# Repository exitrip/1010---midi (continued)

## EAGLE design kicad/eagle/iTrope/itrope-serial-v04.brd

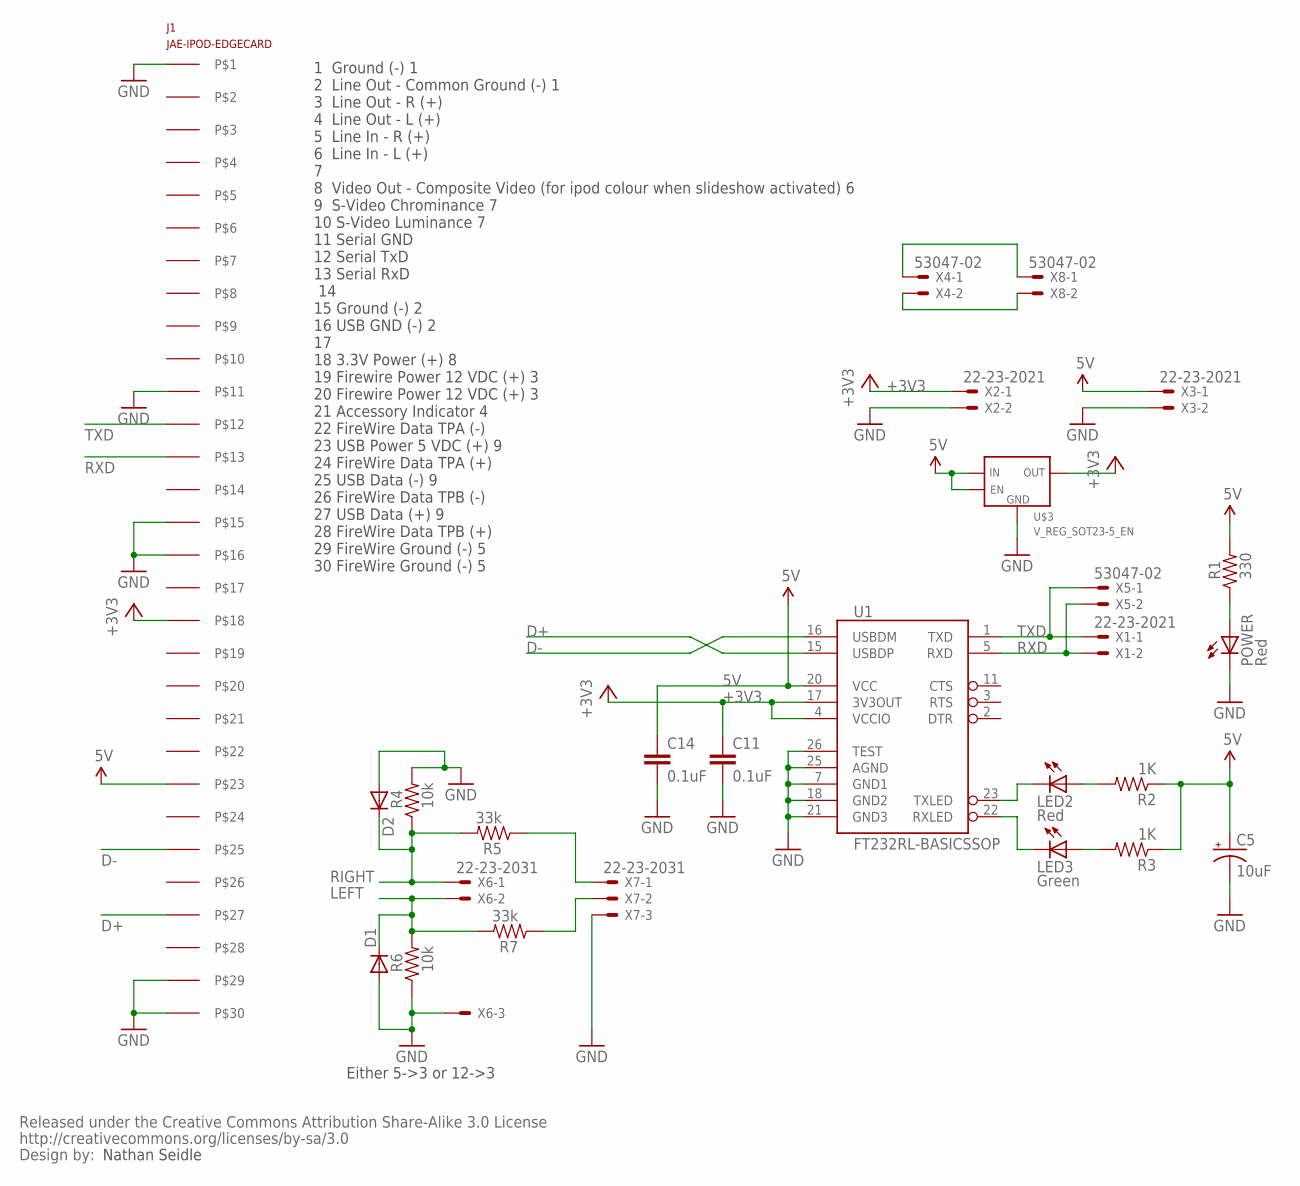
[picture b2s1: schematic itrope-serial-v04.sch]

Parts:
C5: 10uF; EIA3216
C11, C14: 0.1uF; C0402
D1, D2: DIODESOD; SOD-323
J1: JAE-IPOD-EDGECARD; 30PINEDGE
LED2: Red; LED-0603
LED3: Green; LED-0603
POWER: Red; LED-0603
R1: 330; C0402
R2, R3: 1K; C0402
R4, R6: 10k; C0402
R5, R7: 33k; C0402
U1: FT232RL-BASICSSOP; SSOP28DB
U$3: V_REG_SOT23-5_EN; SOT23-5
U$9: CREATIVE_COMMONS
X1, X2, X3: 22-23-2021
X4, X5, X8: 53047-02
X6, X7: 22-23-2031

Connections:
5V: C5.A (+), C14.1, J1.P$23, R1.2, R2.1, R3.1, U1.20 (VCC), U$3.1 (IN), U$3.3 (EN), X3.1
+3V3: C11.1, J1.P$18, U1.4 (VCCIO), U1.17 (3V3OUT), U$3.5 (OUT), X2.1
D+: J1.P$27, U1.15 (USBDP)
D-: J1.P$25, U1.16 (USBDM)
GND: C5.C (-), C11.2, C14.2, D1.2 (A), D2.2 (A), J1.P$1, J1.P$11, J1.P$15, J1.P$16, J1.P$29, J1.P$30, POWER.C, R4.2, R6.1, U1.7 (GND1), U1.18 (GND2), U1.21 (GND3), U1.25 (AGND), U1.26 (TEST), U$3.2 (GND), X2.2, X3.2, X6.3, X7.3
LEFT: D1.1 (C), R6.2, R7.2, X6.2
unnamed: POWER.A, R1.1
unnamed: R7.1, X7.2
unnamed: LED2.A, R2.2
unnamed: LED3.A, R3.2
unnamed: R5.1, X7.1
unnamed: X4.2, X8.2
unnamed: X4.1, X8.1
RIGHT: D2.1 (C), R4.1, R5.2, X6.1
RXD: J1.P$13, U1.5 (RXD), X1.2, X5.2
RXLED: LED3.C, U1.22 (RXLED)
TXD: J1.P$12, U1.1 (TXD), X1.1, X5.1
TXLED: LED2.C, U1.23 (TXLED)

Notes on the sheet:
Nathan Seidle
1 Ground (-) 1 2 Line Out - Common Ground (-) 1 3 Line Out - R (+) 4 Line Out - L (+) 5 Line In - R (+) 6 Line In - L (+) 7 8 Video Out - Composite Video (for ipod colour when slideshow activated) 6 9 S-Video Chrominance 7 10 S-Video Luminance 7 11 Serial GND 12 Serial TxD 13 Serial RxD 14 15 Groun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
Either 5->3 or 12->3

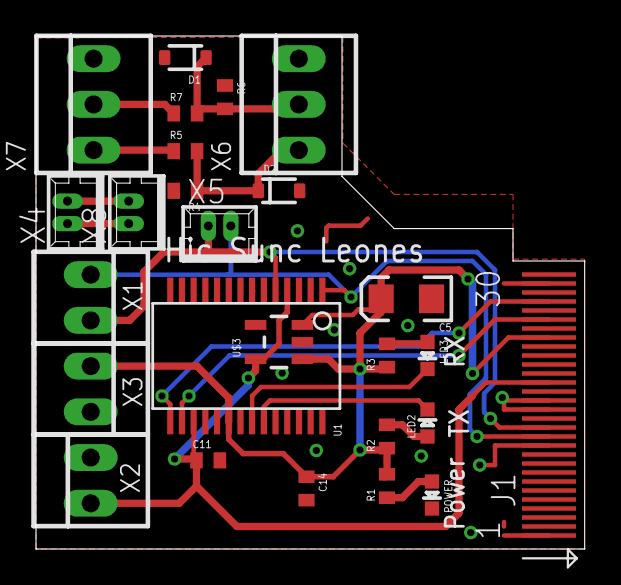
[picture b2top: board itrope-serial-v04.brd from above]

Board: 2 copper layers, 30.5 x 28.5 mm, 27 parts (0 on the bottom side), 18 nets.

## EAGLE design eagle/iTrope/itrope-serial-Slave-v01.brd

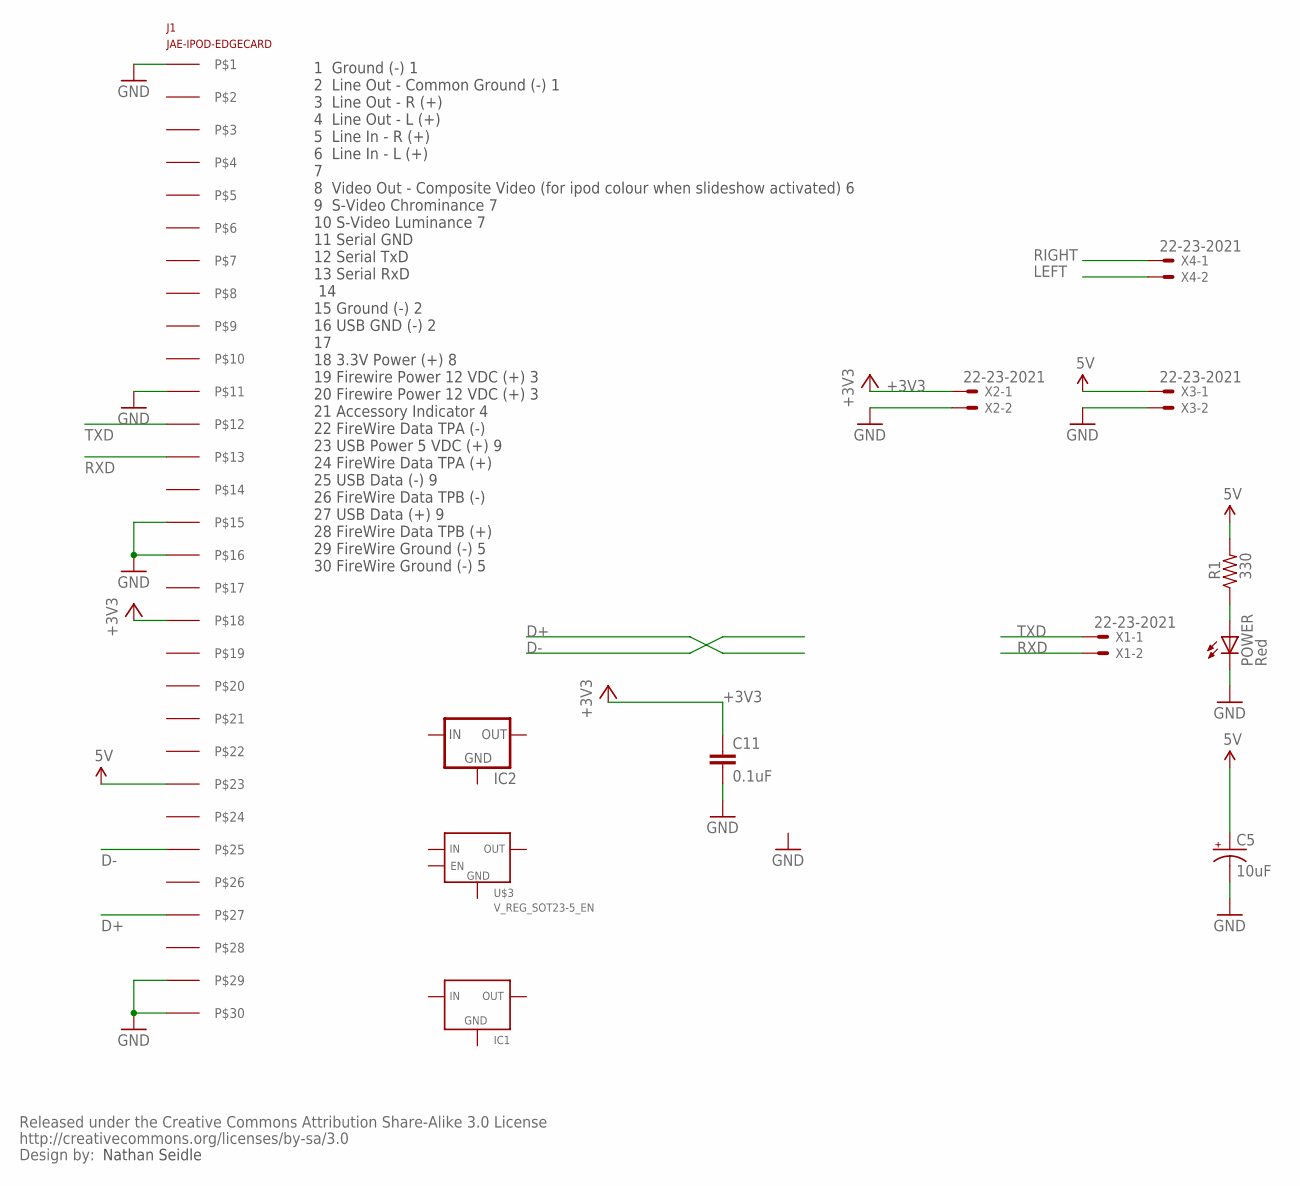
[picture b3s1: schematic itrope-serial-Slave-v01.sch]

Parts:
C5: 10uF; EIA3216
C11: 0.1uF; C0402
IC1: V_REG_LM2937; SOT223
IC2: 78LXX
J1: JAE-IPOD-EDGECARD; 30PINEDGE
POWER: Red; LED-0603
R1: 330; C0402
U$3: V_REG_SOT23-5_EN; SOT23-5
U$9: CREATIVE_COMMONS
X1, X2, X3, X4: 22-23-2021

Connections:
5V: C5.A (+), J1.P$23, R1.2, X3.1
+3V3: C11.1, J1.P$18, X2.1
D+: J1.P$27
D-: J1.P$25
GND: C5.C (-), C11.2, J1.P$1, J1.P$11, J1.P$15, J1.P$16, J1.P$29, J1.P$30, POWER.C, X2.2, X3.2
LEFT: X4.2
unnamed: POWER.A, R1.1
RIGHT: X4.1
RXD: J1.P$13, X1.2
TXD: J1.P$12, X1.1

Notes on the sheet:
Nathan Seidle
1 Ground (-) 1 2 Line Out - Common Ground (-) 1 3 Line Out - R (+) 4 Line Out - L (+) 5 Line In - R (+) 6 Line In - L (+) 7 8 Video Out - Composite Video (for ipod colour when slideshow activated) 6 9 S-Video Chrominance 7 10 S-Video Luminance 7 11 Serial GND 12 Serial TxD 13 Serial RxD 14 15 Groun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

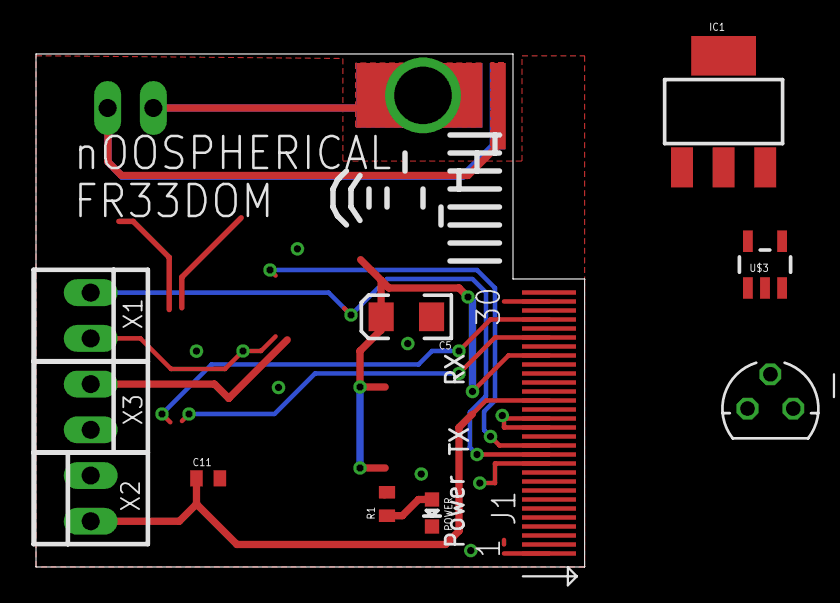
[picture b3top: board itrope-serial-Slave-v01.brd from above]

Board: 2 copper layers, 30.5 x 28.5 mm, 13 parts (1 on the bottom side), 6 nets.

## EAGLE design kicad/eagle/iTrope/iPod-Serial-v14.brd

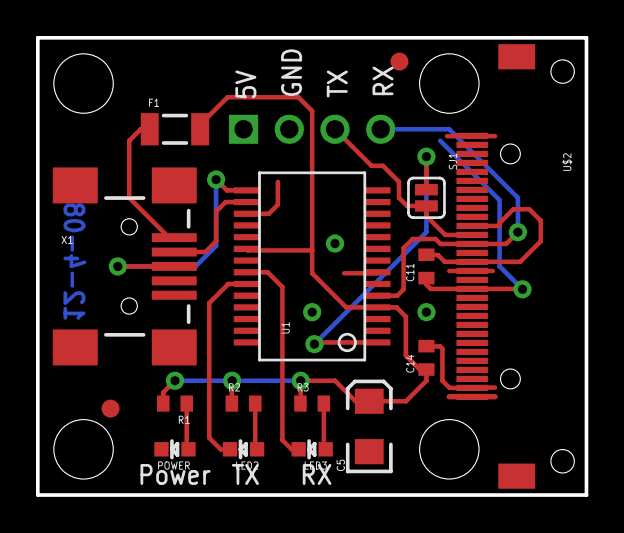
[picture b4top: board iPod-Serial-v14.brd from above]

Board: 2 copper layers, 30.5 x 25.4 mm, 22 parts (1 on the bottom side), 14 nets.

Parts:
C5: 10uF; EIA3216
C11, C14: 0.1uF; C0402
F1: 500mA-PTC; PTC-1206
JP1: 1X04
LED2: Red; LED-0603
LED3: Green; LED-0603
POWER: Red; LED-0603
R1: 330; C0402
R2, R3: 1K; C0402
SJ1: SOLDERJUMPERNC2; SJ_2S
U1: FT232RL-BASICSSOP; SSOP28DB
U$1, U$5, U$6, U$7: STAND-OFF
U$2: IPOD_CONNECTOR_FEMALE; IPOD_FEMALE_CONNECTOR
U$4, U$8: FIDUCIAL1X2; FIDUCIAL-1X2
U$9: CREATIVE_COMMONS
X1: USBSMD; USB-MINIB

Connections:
3.3V: C11.1, U1.17, U$2.18
5V: C5.A, C14.1, F1.2, JP1.1, R1.2, R2.1, R3.1, U1.4, U1.20
GND: C5.C, C11.2, C14.2, JP1.2, POWER.C, U1.7, U1.18, U1.21, U1.25, U1.26, U$2.1, U$2.11, U$2.15, U$2.16, U$2.29, U$2.30, X1.GND
unnamed: POWER.A, R1.1
unnamed: U1.15, X1.D+
unnamed: LED2.A, R2.2
unnamed: LED3.A, R3.2
unnamed: U1.16, X1.D-
RXLED: LED3.C, U1.22
TXD: JP1.3, SJ1.2, U$2.12
TXLED: LED2.C, U1.23
USB-RX: JP1.4, U1.5, U$2.13
USB-TX: SJ1.1, U1.1
USBVCC: F1.1, X1.VBUS

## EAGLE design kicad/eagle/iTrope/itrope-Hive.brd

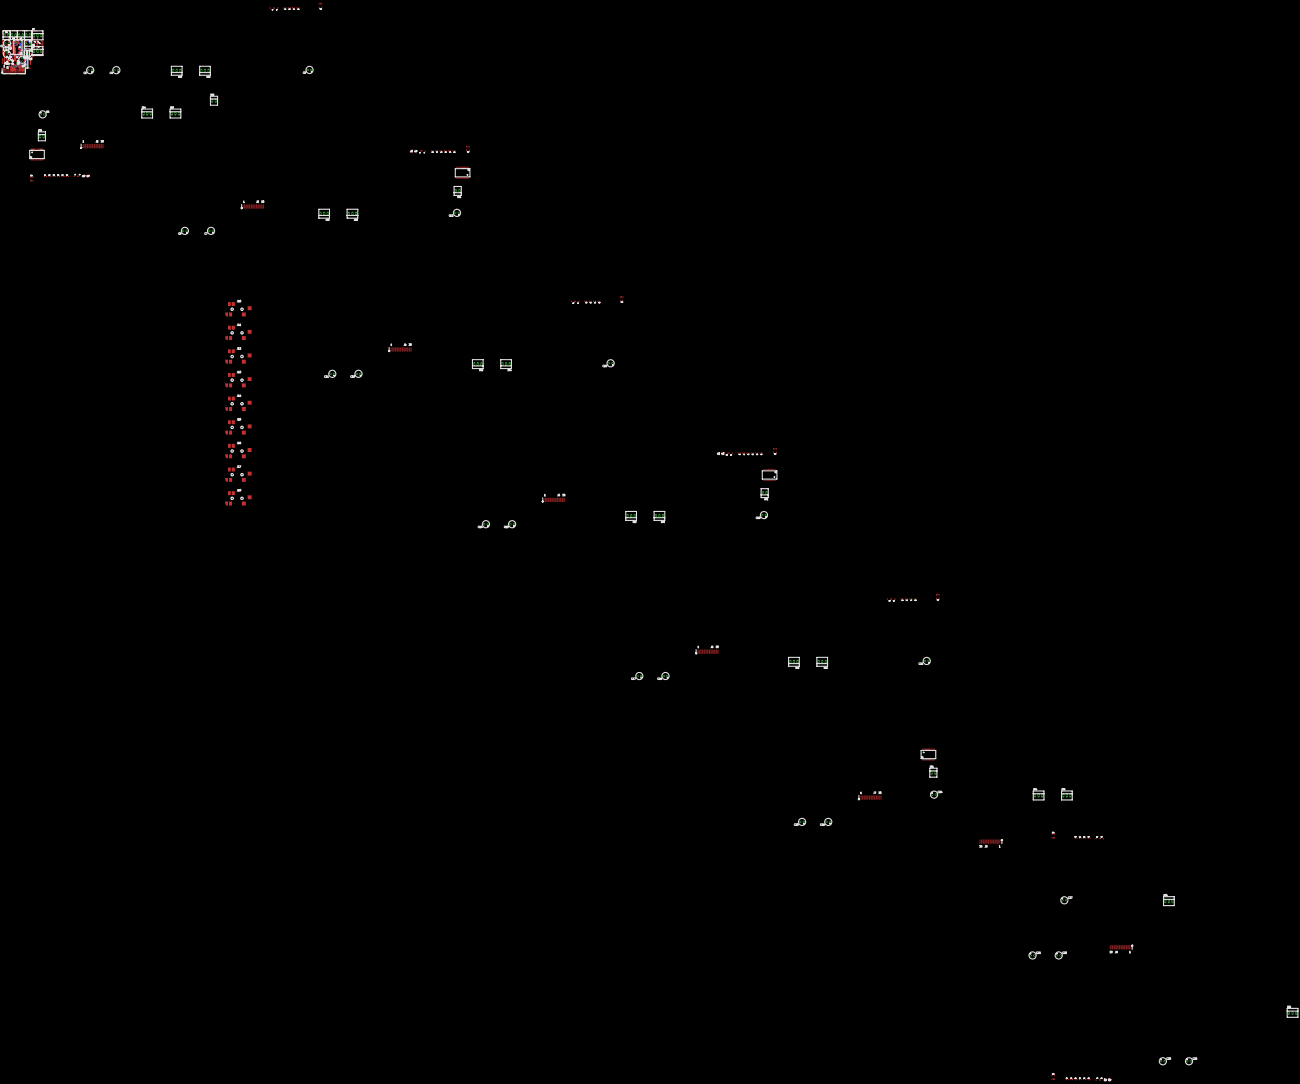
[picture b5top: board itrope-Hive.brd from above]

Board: 2 copper layers, 175 parts (0 on the bottom side), 50 nets.

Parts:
C1, C4, C7, C10, C13, C16, C19, C22, C25: 10uF; E2,5-5
C2, C3, C5, C6, C8, C9, C11, C12, C14, C15, C17, C18, C20, C21, C23, C24, C26, C27: 0.1uF; E2,5-5
D1, D2, D3, D4, D5, D6, D7, D8, D9, D10, D11, D12, D13, D14, D15, D16, D17, D18: SOD-323
J1, J2, J3, J4, J5, J6, J7, J8, J9: ITRIP-V1; 30PINEDGE+ITRIP
J10, J11, J12, J13, J14, J15, J16, J17, J18: CUI-SJ-4351-CUSTOM
LED1, LED2, LED7, LED11, LED15: Red; LED-0603
LED3, LED4, LED8, LED12, LED16: Green; LED-0603
POWER: Red; LED-0603
R1: 330; C0402
R2, R3, R9, R10, R23, R24, R37, R38, R51, R52: 1K; C0402
R4, R6, R11, R13, R18, R20, R25, R27, R32, R34, R39, R41, R46, R48, R53, R55, R60, R62: 10k; C0402
R5, R7, R12, R14, R19, R21, R26, R28, R33, R35, R40, R42, R47, R49, R54, R56, R61, R63: 33k; C0402
U1, U2, U4, U6, U8: FT232RL-BASICSSOP; SSOP28DB
U$3, U$11, U$19, U$26, U$33, U$40, U$47, U$54, U$61: V_REG_SOT23-5_EN; SOT23-5
U$7, U$9, U$16, U$23, U$30, U$37, U$44, U$51, U$58: CREATIVE_COMMONS
X1, X2, X3, X4, X9, X11, X12, X31, X51, X71: 22-23-2021
X5, X8, X10: 87758-0216
X6, X7, X14, X15, X24, X25, X34, X35, X44, X45, X54, X55, X64, X65, X74, X75, X84, X85: 22-23-2031

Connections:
5V: C1.+, C3.+, C4.+, C6.+, C7.+, C9.+, C10.+, C12.+, C13.+, C15.+, C16.+, C18.+, C19.+, C21.+, C22.+, C24.+, C25.+, C27.+, J1.P$23, J2.P$23, J3.P$23, J4.P$23, J5.P$23, J6.P$23, J7.P$23, J8.P$23, J9.P$23, R1.2, R2.1, R3.1, R9.1, R10.1, R23.1, R24.1, R37.1, R38.1, R51.1, R52.1, U1.20, U2.20, U4.20, U6.20, U8.20, U$3.1, U$3.3, U$11.1, U$11.3, U$19.1, U$19.3, U$26.1, U$26.3, U$33.1, U$33.3, U$40.1, U$40.3, U$47.1, U$47.3, U$54.1, U$54.3, U$61.1, U$61.3, X3.1, X8.1
+3V3: C2.+, C5.+, C8.+, C11.+, C14.+, C17.+, C20.+, C23.+, C26.+, J1.P$18, J2.P$18, J3.P$18, J4.P$18, J5.P$18, J6.P$18, J7.P$18, J8.P$18, J9.P$18, U1.4, U1.17, U2.4, U2.17, U4.4, U4.17, U6.4, U6.17, U8.4, U8.17, U$3.5, U$11.5, U$19.5, U$26.5, U$33.5, U$40.5, U$47.5, U$54.5, U$61.5, X2.1, X8.2
D+: J1.P$27, J2.P$27, J3.P$27, J4.P$27, J5.P$27, J6.P$27, J7.P$27, J8.P$27, J9.P$27, U1.15, U2.15, U4.15, U6.15, U8.15
D-: J1.P$25, J2.P$25, J3.P$25, J4.P$25, J5.P$25, J6.P$25, J7.P$25, J8.P$25, J9.P$25, U1.16, U2.16, U4.16, U6.16, U8.16
GND: C1.-, C2.-, C3.-, C4.-, C5.-, C6.-, C7.-, C8.-, C9.-, C10.-, C11.-, C12.-, C13.-, C14.-, C15.-, C16.-, C17.-, C18.-, C19.-, C20.-, C21.-, C22.-, C23.-, C24.-, C25.-, C26.-, C27.-, D1.2, D2.2, D3.2, D4.2, D5.2, D6.2, D7.2, D8.2, D9.2, D10.2, D11.2, D12.2, D13.2, D14.2, D15.2, D16.2, D17.2, D18.2, J1.P$1, J1.P$11, J1.P$15, J1.P$16, J1.P$29, J1.P$30, J2.P$1, J2.P$11, J2.P$15, J2.P$16, J2.P$29, J2.P$30, J3.P$1, J3.P$11, J3.P$15, J3.P$16, J3.P$29, J3.P$30, J4.P$1, J4.P$11, J4.P$15, J4.P$16, J4.P$29, J4.P$30, J5.P$1, J5.P$11, J5.P$15, J5.P$16, J5.P$29, J5.P$30, J6.P$1, J6.P$11, J6.P$15, J6.P$16, J6.P$29, J6.P$30, J7.P$1, J7.P$11, J7.P$15, J7.P$16, J7.P$29, J7.P$30, J8.P$1, J8.P$11, J8.P$15, J8.P$16, J8.P$29, J8.P$30, J9.P$1, J9.P$11, J9.P$15, J9.P$16, J9.P$29, J9.P$30, J10.1, J10.4, J11.1, J11.4, J12.1, J12.4, J13.1, J13.4, J14.1, J14.4, J15.1, J15.4, J16.1, J16.4, J17.1, J17.4, J18.1, J18.4, POWER.C, R4.2, R6.1, R11.2, R13.1, R18.2, R20.1, R25.2, R27.1, R32.2, R34.1, R39.2, R41.1, R46.2, R48.1, R53.2, R55.1, R60.2, R62.1, U1.7, U1.18, U1.21, U1.25, U1.26, U2.7, U2.18, U2.21, U2.25, U2.26, U4.7, U4.18, U4.21, U4.25, U4.26, U6.7, U6.18, U6.21, U6.25, U6.26, U8.7, U8.18, U8.21, U8.25, U8.26, U$3.2, U$11.2, U$19.2, U$26.2, U$33.2, U$40.2, U$47.2, U$54.2, U$61.2, X2.2, X3.2, X6.3, X7.3, X10.1, X10.2, X14.3, X15.3, X24.3, X25.3, X34.3, X35.3, X44.3, X45.3, X54.3, X55.3, X64.3, X65.3, X74.3, X75.3, X84.3, X85.3
LEFT: D1.1, D3.1, D5.1, D7.1, D9.1, D11.1, D13.1, D15.1, D17.1, R6.2, R7.2, R13.2, R14.2, R20.2, R21.2, R27.2, R28.2, R34.2, R35.2, R41.2, R42.2, R48.2, R49.2, R55.2, R56.2, R62.2, R63.2, X6.2, X14.2, X24.2, X34.2, X44.2, X54.2, X64.2, X74.2, X84.2
unnamed: POWER.A, R1.1
unnamed: R7.1, X7.2
unnamed: LED2.A, R2.2
unnamed: LED3.A, R3.2
unnamed: R5.1, X7.1
unnamed: LED1.A, R9.2
unnamed: LED4.A, R10.2
unnamed: R14.1, X15.2
unnamed: R12.1, X15.1
unnamed: R21.1, X25.2
unnamed: R19.1, X25.1
unnamed: LED7.A, R23.2
unnamed: LED8.A, R24.2
unnamed: R28.1, X35.2
unnamed: R26.1, X35.1
unnamed: R35.1, X45.2
unnamed: R33.1, X45.1
unnamed: LED11.A, R37.2
unnamed: LED12.A, R38.2
unnamed: R42.1, X55.2
unnamed: R40.1, X55.1
unnamed: R49.1, X65.2
unnamed: R47.1, X65.1
unnamed: LED15.A, R51.2
unnamed: LED16.A, R52.2
unnamed: R56.1, X75.2
unnamed: R54.1, X75.1
unnamed: R63.1, X85.2
unnamed: R61.1, X85.1
RIGHT: D2.1, D4.1, D6.1, D8.1, D10.1, D12.1, D14.1, D16.1, D18.1, R4.1, R5.2, R11.1, R12.2, R18.1, R19.2, R25.1, R26.2, R32.1, R33.2, R39.1, R40.2, R46.1, R47.2, R53.1, R54.2, R60.1, R61.2, X6.1, X14.1, X24.1, X34.1, X44.1, X54.1, X64.1, X74.1, X84.1
RXD: J2.P$13, J3.P$13, J4.P$13, J5.P$13, J6.P$13, J7.P$13, J8.P$13, J9.P$13, U2.5, U4.5, U6.5, U8.5, X11.2, X12.2, X31.2, X51.2, X71.2
RXD_COORD: J1.P$13, U1.5, X1.2, X4.2
RXLED: LED3.C, U1.22
RXLED1: LED4.C, U2.22
RXLED3: LED8.C, U4.22
RXLED5: LED12.C, U6.22
RXLED7: LED16.C, U8.22
TXD: J2.P$12, J3.P$12, J4.P$12, J5.P$12, J6.P$12, J7.P$12, J8.P$12, J9.P$12, U2.1, U4.1, U6.1, U8.1, X11.1, X12.1, X31.1, X51.1, X71.1
TXD_COORD: J1.P$12, U1.1, X1.1, X4.1
TXLED: LED2.C, U1.23
TXLED1: LED1.C, U2.23
TXLED3: LED7.C, U4.23
TXLED5: LED11.C, U6.23
TXLED7: LED15.C, U8.23

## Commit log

2015-12-05 initial commit for exitrip code
2015-12-05 add gitignore
2015-12-05 untrack object etc...
2015-12-06 Fix Up/Down glissandi... updateNote() didn't work with uartRX rupt completely...
2015-12-06 forgot about Blinky optins
2015-12-09 fix updown effecting both voices
2016-01-04 add happy song, some comments and fix some bugs
2016-03-26 has one meh song....
2016-03-26 first stab at songdata segregation with fixed address songBook...
2016-03-26 move linker settings from sim to EMU
2016-03-27 not working
2016-03-27 fix riff type
2016-03-28 relocation working but self prog not on emulator... atleast according to the memory view from the IDE
2016-04-06 Getting a 'set bootstat then reboot for flash magic' usb loader working
2016-04-06 remove v3 ISP
2016-04-06 fuck yeah!!! give a magic sysEX or hold midButt at power on to set bootstat -> enter flashMagic bootloader
2016-04-20 got good things going
2016-04-20 fix peace song
2016-04-20 add stereo on/off
2016-04-23 tested stereo toggle and stereo control
2016-04-29 add songrePeat flag and vexations Parts
2016-04-30 got looPsongs working with a new songFlags deal... workers can now looP on their lonesome too
2016-05-27 really slow , spread spectrum vexations only, autostart seems to work well... added a setFreq which works from boot!!! its late
2016-06-18 sump show or there about
2016-06-18 This has the boot entry disabled... cause its a killer for workshops
2016-06-18 turn LED on at boot for Power ind...
2016-06-22 bring in adc code
2016-06-22 add sin LUTs
2016-06-22 add DACout to each timer... each write to DAC is a good number of instructions
2016-07-07 add ee files
2016-07-13 first stab at adc0 and dac1 out for both coord and basics
2016-07-13 comment out playGate, cause it really bungs the interface up
2016-07-17 commit unit11 opening state
2016-09-11 ctrl-S
2016-10-05 getting working
2016-10-08 fix polarity of CV control and turn on STEREO from boot
2016-11-23 put test patches in a safe place
2016-11-26 got note creation working ok, timer overflow still broken
2016-11-26 timer overflow fixed
2016-11-27 almost got a c file... still no curly brackets...
2016-12-26 working on processing programs
2017-01-21 fix this one wierd compiler error with settings
2017-01-21 add more code space
2017-01-21 more unitXII'ing
2017-01-21 add adc03 define
2017-01-22 update adcin
2017-01-22 add interrupt garuda inside txProg() and fix glaring note->station_down bug/typo...
2017-01-23 have a robust single gate input coordinator and gate+CV input for transmitter quirky but not unusable
2017-01-25 i think we are actually erasing.... maybe its a conf bit thing....
2017-01-25 programming with 3v3 and 5V arduinos works headless atleast!!!!! add script to wrap xxd -i array
2017-01-25 crtl-s
2017-01-25 shift pinout to skip builtin led / unlucky pin
2017-01-25 ctrl-s debuggging unit modes
2017-03-23 add eagle files for cloudgods
2017-04-06 cntrl s on lots of work...
2017-04-09 freeze hive as submitted to PCBway
2017-04-09 DAC out to follow audio pitch... so that we can FM with CV
2017-04-09 actually do last commit and rm pcb folder
2017-04-09 clean up dac code a bit
2017-04-09 update LUTFreq and ???
2017-04-10 return LUTFreq and tweak timing of output interrupts... add stereo_tog to accepted external commands and ... add VNote/LNote to updateNote() ... and cleave off 256 bytes from the unused sysEx xdata b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
2017-05-18 got a ram based channel address scheme compiling
2017-05-26 add some ui to puredata stuff
2017-06-04 fix deadly pin assignment bug in mini pro code
2017-09-05 add a script that will load .hex file with to numbers that should in turn get loaded as channels
2017-09-06 script now detects and overwrites old channels
2017-09-06 add untested code in arduino programmer to insert defined midi channels dynamically
2017-09-06 update code alignment in linker, update scripts
2017-09-06 program time channel selection through arduino works!!! kinda... Lchan always responds....
2017-09-07 fixed a whole lot of minor and fatal things.... decent error checking of channels at start up and general behaviour.... arduino and script work ok...
2018-01-03 tweak eagle board and sundries
2018-03-24 add uV5 project
2018-04-04 save basic project
2018-04-04 add more visual and midi pd stuff
2018-04-22 update pd patches
2018-04-27 remove random pure-data patches
2018-04-27 working on osc control for big arrays
2018-08-12 trying to get merge to compile
2018-09-22 add new oscSwitch multi page setup
2020-02-02 push newer pd files
2020-02-02 got it compiling and hope to have fixed the note off bug
2020-02-02 add oscRouter and new polyphonic stuff... note off now twerks
2022-05-07 need to compare to whats on github
2022-05-13 add Pitch bend to L and V chan, untested
2023-09-17 just want to slurp oscRouter change, but i remember this firmware working
2023-11-25 update with headless linux setup
2023-11-25 try for duration feedback
2023-11-25 fix duration feedback
2023-11-25 remove scale feedback
2023-11-25 fix several typos
2023-11-25 sync touch and pd settings
2023-11-25 wierd that limits didnt get set in other commit
2023-11-25 found the global range loadband
2023-11-25 fix statscale response... have metroscale effect all metros live
2024-07-12 add newer, almost finished kicad schematic
2024-08-25 tweak kicad a bit
2024-08-26 got a wordy, but decent README up
2024-08-26 cleave off programmer instructions
2024-08-26 fix file rename
2024-08-26 foldres...
2024-08-26 file.s......
2024-08-26 images....
2024-08-26 spaces, and images
2024-08-29 markup png
2024-09-01 define mask out all the channel setting code that expects more complex itrip firmware
